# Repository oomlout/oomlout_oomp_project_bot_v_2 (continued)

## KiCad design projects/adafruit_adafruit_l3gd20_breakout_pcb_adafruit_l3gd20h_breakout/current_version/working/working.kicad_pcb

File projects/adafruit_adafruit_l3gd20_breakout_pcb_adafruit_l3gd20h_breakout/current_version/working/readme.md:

# adafruit_l3gd20_breakout_pcb
 
## summary 
* id: adafruit_adafruit_l3gd20_breakout_pcb_adafruit_l3gd20h_breakout
* user: adafruit
* name: adafruit_l3gd20_breakout_pcb
* board: adafruit_l3gd20h_breakout
* repo: https://github.com/adafruit/Adafruit-L3GD20-Breakout-PCB

* src_file_repo_sch: 
* src_file_repo_sch_link: https://github.com/adafruit/Adafruit-L3GD20-Breakout-PCB/tree/master/
* full details link: https://github.com/oomlout/oomlout_oomp_project_bot_v_2/tree/main/projects/adafruit_adafruit_l3gd20_breakout_pcb_adafruit_l3gd20h_breakout/current_version/working  

## schematic  
  
[schematic (pdf)](working_schematic.pdf) 

## pcb  

[board (pdf)](working.pdf)  

## working_bom
| Id | Designator | Footprint | Quantity | Designation | Supplier and ref |  | None | 
| --- | --- | --- | --- | --- | --- | --- | --- | 
| 1 | U$12,U$11,U$14,U$13 | MOUNTINGHOLE_2.0_PLATED | 4 | MOUNTINGHOLE2.0 |  |  | [''] | 
| 2 | U$15,U$16 | FIDUCIAL_1MM | 2 | FIDUCIAL |  |  | [''] | 
| 3 | R6,R3 | _0805MP | 2 | 10K |  |  | [''] | 
| 4 | R2,R5,R4,R7 | 0805-NO | 4 | 10K |  |  | [''] | 
| 5 | IC2 | L3GD20H_LGA16L | 1 | LGD20H |  |  | [''] | 
| 6 | C4,C1 | 0805-NO | 2 | 0.1uF |  |  | [''] | 
| 7 | D1 | SOD-323F | 1 | 1N4148 |  |  | [''] | 
| 8 | IC1 | SOT23-5L | 1 | MIC5225-3.3 |  |  | [''] | 
| 9 | U$3 | SYMBOL_GYROXYZ_10MM | 1 |  |  |  | [''] | 
| 10 | Q1,Q2 | SOT23 | 2 | BSS138 |  |  | [''] | 
| 11 | C5,C3 | 0805-NO | 2 | 10uF |  |  | [''] | 
| 12 | JP1 | 1X09_ROUND_76 | 1 |  |  |  | [''] | 
| 13 | U$10 | ADAFRUIT_TEXT_20MM | 1 |  |  |  | [''] | 

## bom_schematic
| Ref | Qnty | Value | Cmp name | Footprint | Description | Vendor | DNP | 
| --- | --- | --- | --- | --- | --- | --- | --- | 
| C1, C4 | 2 | 0.1uF | CAP_CERAMIC0805-NOOUTLINE | working:0805-NO |  |  |  | 
| C3, C5 | 2 | 10uF | CAP_CERAMIC0805-NOOUTLINE | working:0805-NO |  |  |  | 
| D1 | 1 | 1N4148 | DIODESOD-323F | working:SOD-323F |  |  |  | 
| IC1 | 1 | LP298XS | LP298XS | working:SOT23-5L |  |  |  | 
| IC2 | 1 | LGD20H | GYRO_L3GD20H | working:L3GD20H_LGA16L |  |  |  | 
| JP1 | 1 | HEADER-1X976MIL | HEADER-1X976MIL | working:1X09_ROUND_76 |  |  |  | 
| Q1, Q2 | 2 | BSS138 | MOSFET-NREFLOW | working:SOT23 |  |  |  | 
| R2, R4, R5, R7 | 4 | 10K | RESISTOR0805_NOOUTLINE | working:0805-NO |  |  |  | 
| R3, R6 | 2 | 10K | RESISTOR_0805MP | working:_0805MP |  |  |  | 
| U$11, U$12, U$13, U$14 | 4 | MOUNTINGHOLE2.0 | MOUNTINGHOLE2.0 | working:MOUNTINGHOLE_2.0_PLATED |  |  |  | 
| U$15, U$16 | 2 | FIDUCIAL | FIDUCIAL | working:FIDUCIAL_1MM |  |  |  | 

## mounting_holes
| x | y | package | value | ref | size | 
| --- | --- | --- | --- | --- | --- | 
| 25.4 | 12.83 | MOUNTINGHOLE_2.0_PLATED | MOUNTINGHOLE2.0 | U$11 | m3 | 
| 0.0 | 12.83 | MOUNTINGHOLE_2.0_PLATED | MOUNTINGHOLE2.0 | U$12 | m3 | 
| 0.0 | 0.0 | MOUNTINGHOLE_2.0_PLATED | MOUNTINGHOLE2.0 | U$13 | m3 | 
| 25.4 | 0.0 | MOUNTINGHOLE_2.0_PLATED | MOUNTINGHOLE2.0 | U$14 | m3 |

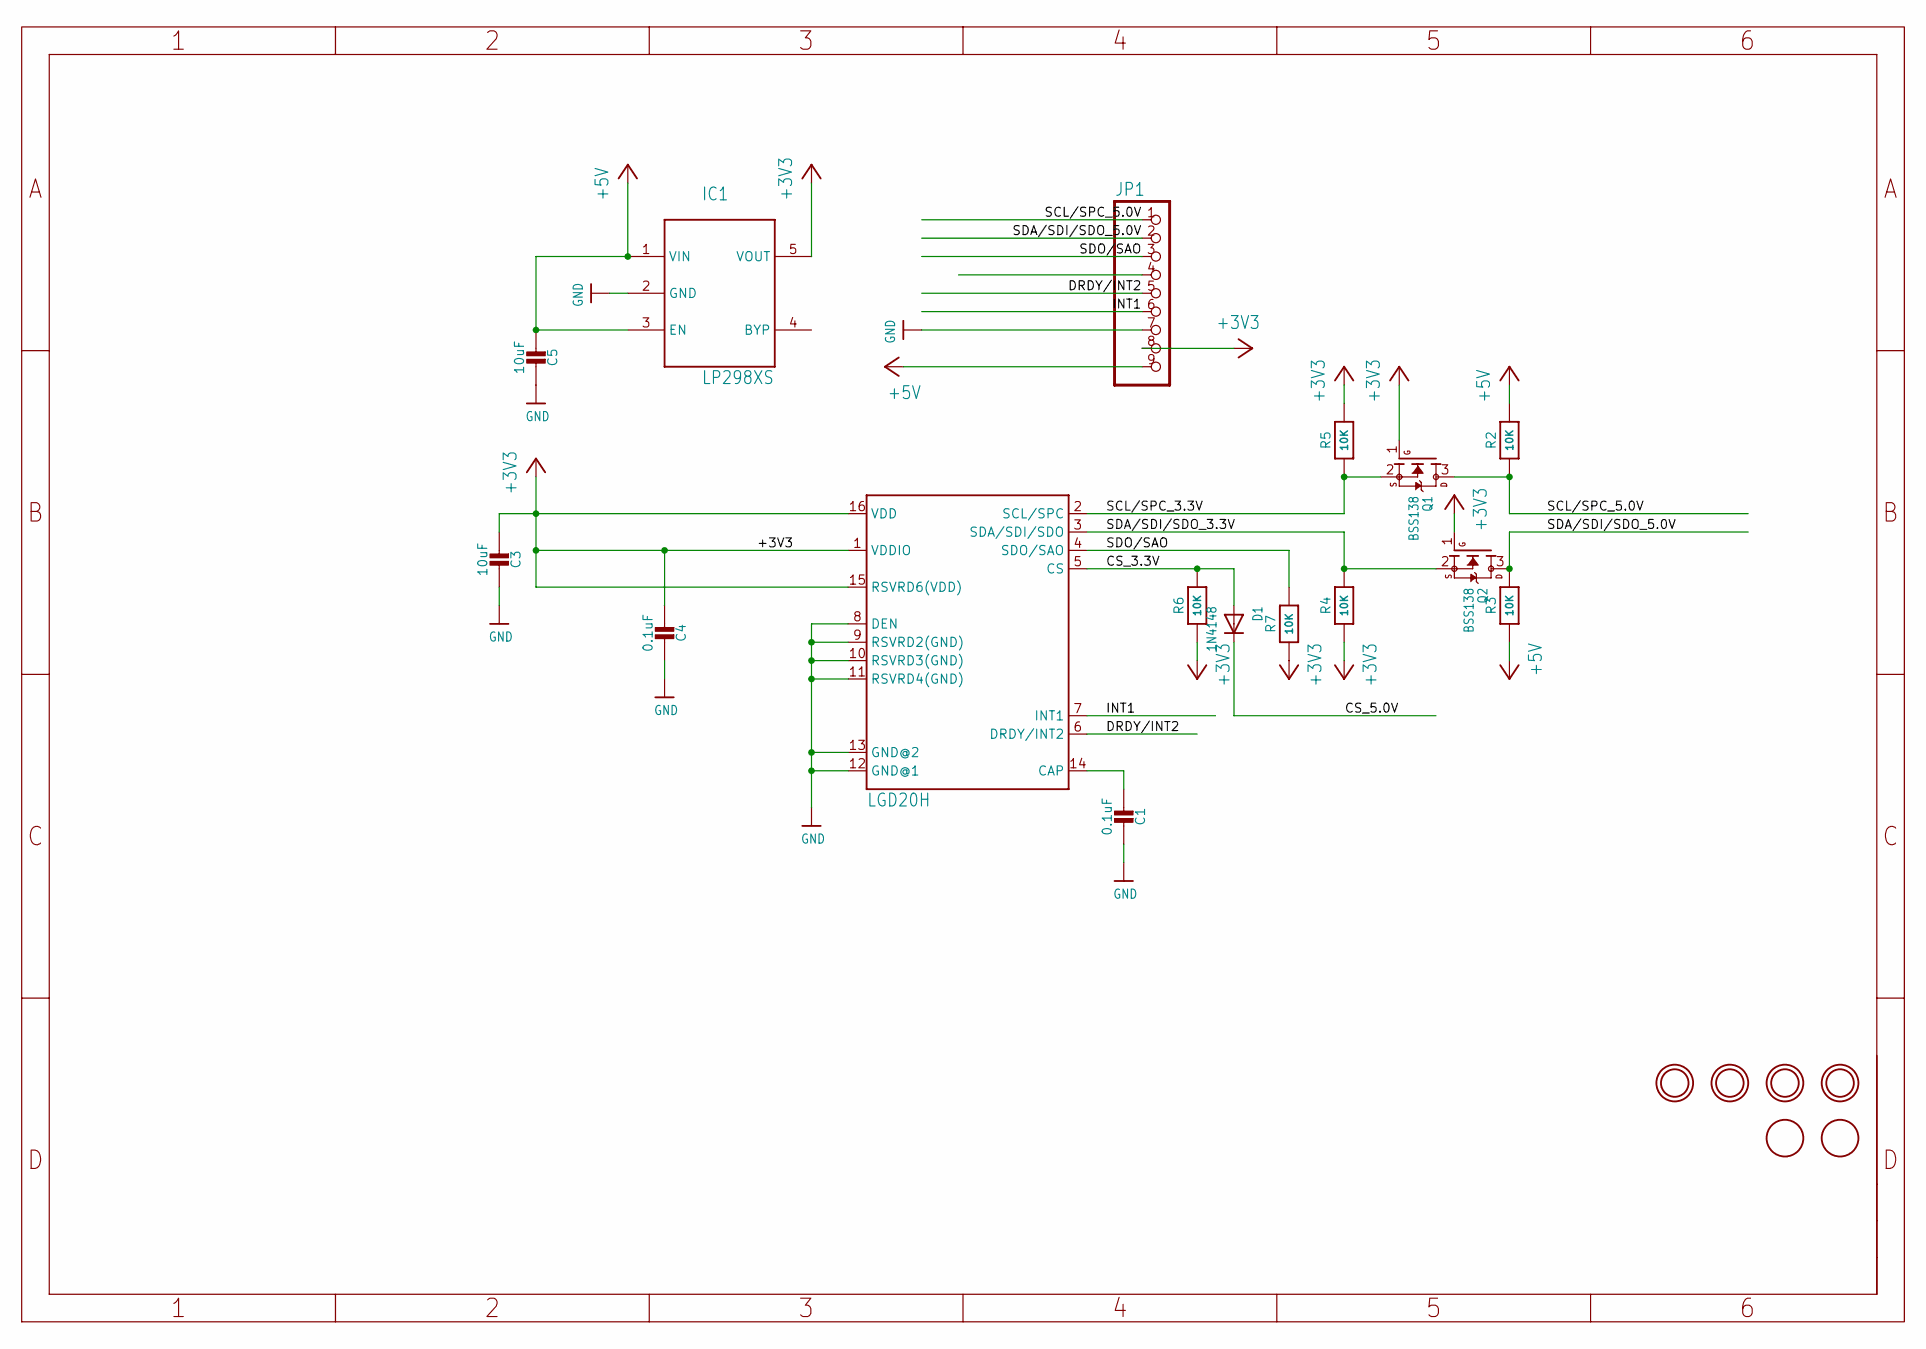
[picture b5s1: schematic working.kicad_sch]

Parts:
C1, C4: 0.1uF; 0805-NO
C3, C5: 10uF; 0805-NO
D1: 1N4148; SOD-323F
IC1: LP298XS; SOT23-5L
IC2: LGD20H; L3GD20H_LGA16L
JP1: HEADER-1X976MIL; 1X09_ROUND_76
Q1, Q2: BSS138; SOT23
R2, R4, R5, R7: 10K; 0805-NO
R3, R6: 10K; _0805MP
U$11, U$12, U$13, U$14: MOUNTINGHOLE2.0; MOUNTINGHOLE_2.0_PLATED
U$15, U$16: FIDUCIAL; FIDUCIAL_1MM

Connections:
+3V3: C3.2, C4.2, IC1.5 (VOUT), IC2.1 (VDDIO), IC2.15 (RSVRD6(VDD)), IC2.16 (VDD), JP1.8, Q1.1 (G), Q2.1 (G), R4.1, R5.2, R6.1, R7.1
+5V: C5.2, IC1.1 (VIN), IC1.3 (EN), JP1.9, R2.2, R3.1
CS_3.3V: D1.A, IC2.5 (CS), R6.2
CS_5.0V: D1.C, JP1.4
DRDY/INT2: IC2.6 (DRDY/INT2), JP1.5
GND: C1.1, C3.1, C4.1, C5.1, IC1.2 (GND), IC2.8 (DEN), IC2.9 (RSVRD2(GND)), IC2.10 (RSVRD3(GND)), IC2.11 (RSVRD4(GND)), IC2.12 (GND@1), IC2.13 (GND@2), JP1.7
INT1: IC2.7 (INT1), JP1.6
unnamed: C1.2, IC2.14 (CAP)
SCL/SPC_3.3V: IC2.2 (SCL/SPC), Q1.2 (S), R5.1
SCL/SPC_5.0V: JP1.1, Q1.3 (D), R2.1
SDA/SDI/SDO_3.3V: IC2.3 (SDA/SDI/SDO), Q2.2 (S), R4.2
SDA/SDI/SDO_5.0V: JP1.2, Q2.3 (D), R3.2
SDO/SAO: IC2.4 (SDO/SAO), JP1.3, R7.2

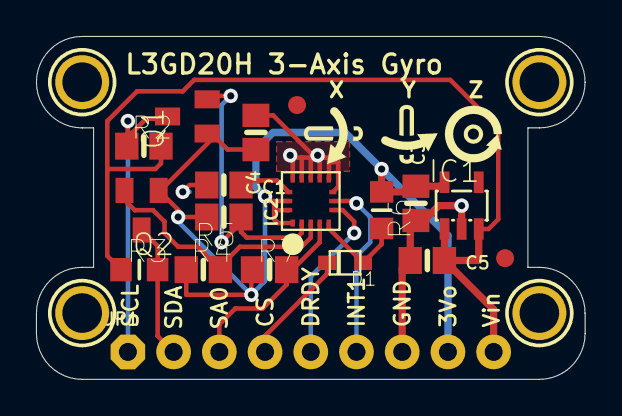
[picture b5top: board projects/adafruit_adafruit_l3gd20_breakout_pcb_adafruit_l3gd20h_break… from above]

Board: 2 copper layers, 30.5 x 19.0 mm, 24 parts (1 on the bottom side), 13 nets.

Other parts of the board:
U$3: SYMBOL_GYROXYZ_10MM
U$10: ADAFRUIT_TEXT_20MM

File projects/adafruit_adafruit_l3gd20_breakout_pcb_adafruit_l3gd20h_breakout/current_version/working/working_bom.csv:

"Id";"Designator";"Footprint";"Quantity";"Designation";"Supplier and ref";
1;"U$12,U$11,U$14,U$13";"MOUNTINGHOLE_2.0_PLATED";4;"MOUNTINGHOLE2.0";;;
2;"U$15,U$16";"FIDUCIAL_1MM";2;"FIDUCIAL";;;
3;"R6,R3";"_0805MP";2;"10K";;;
4;"R2,R5,R4,R7";"0805-NO";4;"10K";;;
5;"IC2";"L3GD20H_LGA16L";1;"LGD20H";;;
6;"C4,C1";"0805-NO";2;"0.1uF";;;
7;"D1";"SOD-323F";1;"1N4148";;;
8;"IC1";"SOT23-5L";1;"MIC5225-3.3";;;
9;"U$3";"SYMBOL_GYROXYZ_10MM";1;"";;;
10;"Q1,Q2";"SOT23";2;"BSS138";;;
11;"C5,C3";"0805-NO";2;"10uF";;;
12;"JP1";"1X09_ROUND_76";1;"";;;
13;"U$10";"ADAFRUIT_TEXT_20MM";1;"";;;

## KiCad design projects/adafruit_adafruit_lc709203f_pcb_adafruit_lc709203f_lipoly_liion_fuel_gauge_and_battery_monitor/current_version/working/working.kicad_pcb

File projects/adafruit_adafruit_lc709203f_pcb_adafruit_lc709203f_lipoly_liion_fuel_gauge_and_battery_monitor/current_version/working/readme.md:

# adafruit_lc709203f_pcb
 
## summary 
* id: adafruit_adafruit_lc709203f_pcb_adafruit_lc709203f_lipoly_liion_fuel_gauge_and_battery_monitor
* user: adafruit
* name: adafruit_lc709203f_pcb
* board: adafruit_lc709203f_lipoly_liion_fuel_gauge_and_battery_monitor
* repo: https://github.com/adafruit/Adafruit-LC709203F-PCB

* src_file_repo_sch: 
* src_file_repo_sch_link: https://github.com/adafruit/Adafruit-LC709203F-PCB/tree/master/
* full details link: https://github.com/oomlout/oomlout_oomp_project_bot_v_2/tree/main/projects/adafruit_adafruit_lc709203f_pcb_adafruit_lc709203f_lipoly_liion_fuel_gauge_and_battery_monitor/current_version/working  

## schematic  
  
[schematic (pdf)](working_schematic.pdf) 

## pcb  

[board (pdf)](working.pdf)  

## working_bom
| Id | Designator | Footprint | Quantity | Designation | Supplier and ref |  | None | 
| --- | --- | --- | --- | --- | --- | --- | --- | 
| 1 | U$21,U$19 | MOUNTINGHOLE_2.5_PLATED | 2 | MOUNTINGHOLE2.5 |  |  | [''] | 
| 2 | CONN3,CONN4 | JST_SH4 | 2 | STEMMA_I2C_QT |  |  | [''] | 
| 3 | @HOLE1,@HOLE0 |  | 2 |  |  |  | [''] | 
| 4 | X1,X2 | JSTPH2_BATT | 2 | JST 2 PH |  |  | [''] | 
| 5 | JP1 | 1X06_ROUND_70 | 1 |  |  |  | [''] | 
| 6 | D1 | CHIPLED_0603_NOOUTLINE | 1 | GREEN |  |  | [''] | 
| 7 | FID4,FID3 | FIDUCIAL_1MM | 2 | FIDUCIAL_1MM |  |  | [''] | 
| 8 | IC1 | WDFN8_3X4_0.65 | 1 | LC709203F |  |  | [''] | 
| 9 | R4 | 0603-NO | 1 | 100 |  |  | [''] | 
| 10 | C1 | 0603-NO | 1 | 1uF |  |  | [''] | 
| 11 | R3 | RESPACK_4X0603 | 1 | 10K |  |  | [''] | 
| 12 | U$22 | ADAFRUIT_3.5MM | 1 |  |  |  | [''] | 
| 13 | R1 | 0603-NO | 1 | 10K |  |  | [''] | 
| 14 | SJ1 | SOLDERJUMPER_CLOSEDWIRE | 1 |  |  |  | [''] | 
| 15 | U$25 | PCBFEAT-REV-040 | 1 |  |  |  | [''] | 
| 16 | U$30,U$31 | STEMMAQT | 2 |  |  |  | [''] | 

## bom_schematic
| Ref | Qnty | Value | Cmp name | Footprint | Description | Vendor | DNP | 
| --- | --- | --- | --- | --- | --- | --- | --- | 
| C1 | 1 | 1uF | CAP_CERAMIC0603_NO | working:0603-NO |  |  |  | 
| CONN3, CONN4 | 2 | STEMMA_I2C_QT | STEMMA_I2C_QT | working:JST_SH4 |  |  |  | 
| D1 | 1 | GREEN | LED0603_NOOUTLINE | working:CHIPLED_0603_NOOUTLINE |  |  |  | 
| FID3, FID4 | 2 | FIDUCIAL_1MM | FIDUCIAL_1MM | working:FIDUCIAL_1MM |  |  |  | 
| IC1 | 1 | LC709203F | LC709203F | working:WDFN8_3X4_0.65 |  |  |  | 
| JP1 | 1 | HEADER-1X670MIL | HEADER-1X670MIL | working:1X06_ROUND_70 |  |  |  | 
| R1 | 1 | 10K | RESISTOR_0603_NOOUT | working:0603-NO |  |  |  | 
| R3 | 1 | 10K | RESISTOR_4PACK | working:RESPACK_4X0603 |  |  |  | 
| R4 | 1 | 100 | RESISTOR_0603_NOOUT | working:0603-NO |  |  |  | 
| SJ1 | 1 | SOLDERJUMPERCLOSED | SOLDERJUMPERCLOSED | working:SOLDERJUMPER_CLOSEDWIRE |  |  |  | 
| U$19, U$21 | 2 | MOUNTINGHOLE2.5 | MOUNTINGHOLE2.5 | working:MOUNTINGHOLE_2.5_PLATED |  |  |  | 
| X1, X2 | 2 | JST 2 PH | CON_JST_PH_2PIN_BATT | working:JSTPH2_BATT |  |  |  | 

## mounting_holes
| x | y | package | value | ref | size | 
| --- | --- | --- | --- | --- | --- | 
| 0.0 | 0.0 | MOUNTINGHOLE_2.5_PLATED | MOUNTINGHOLE2.5 | U$19 | m3 | 
| 20.32 | 0.0 | MOUNTINGHOLE_2.5_PLATED | MOUNTINGHOLE2.5 | U$21 | m3 |

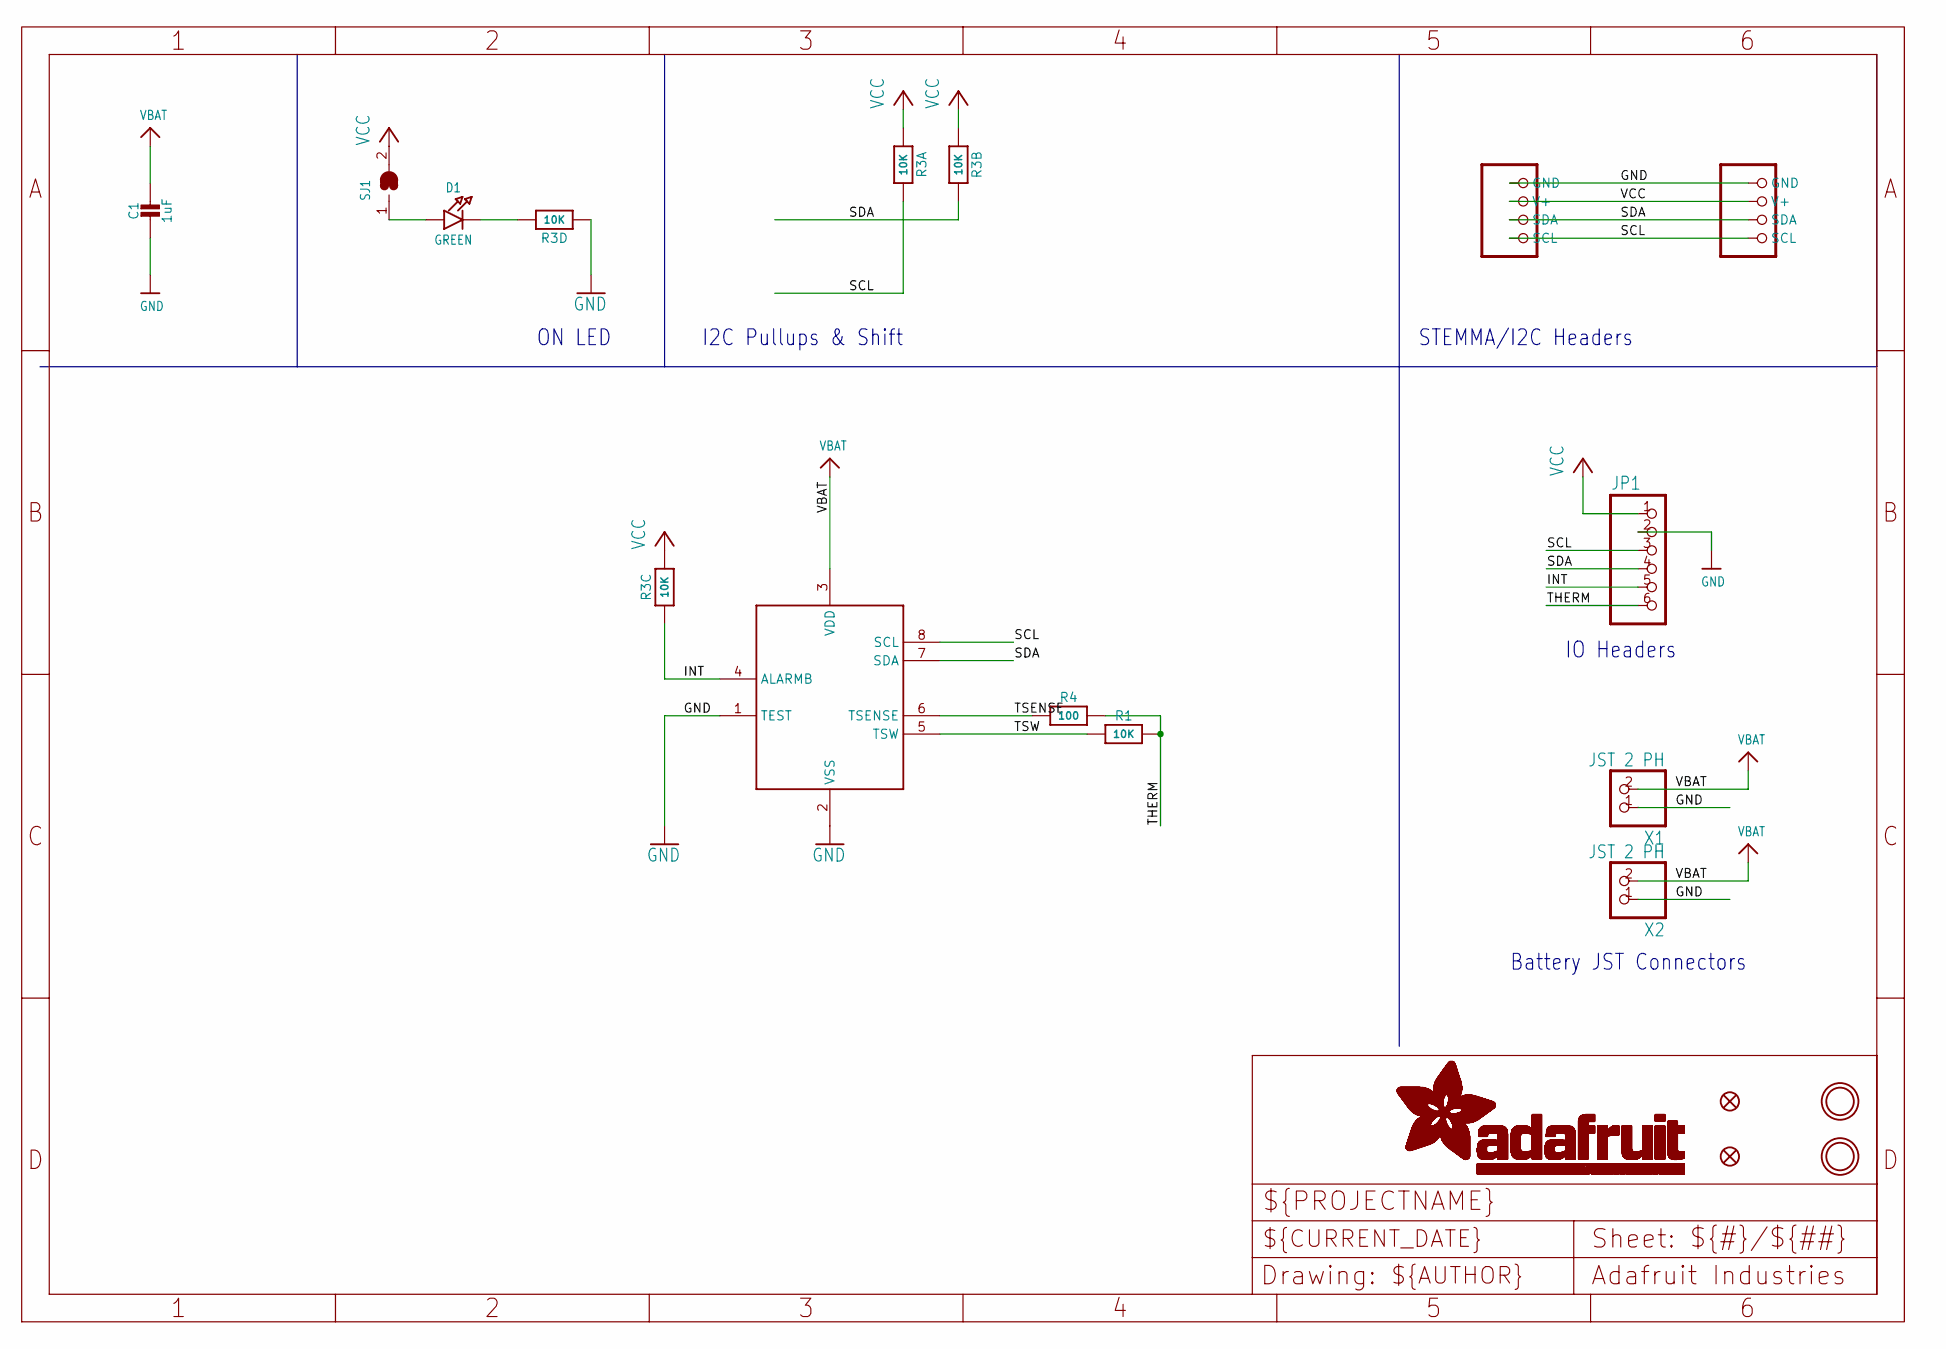
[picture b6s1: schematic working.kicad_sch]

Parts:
C1: 1uF; 0603-NO
CONN3, CONN4: STEMMA_I2C_QT; JST_SH4
D1: GREEN; CHIPLED_0603_NOOUTLINE
FID3, FID4: FIDUCIAL_1MM
IC1: LC709203F; WDFN8_3X4_0.65
JP1: HEADER-1X670MIL; 1X06_ROUND_70
R1: 10K; 0603-NO
R3: 10K; RESPACK_4X0603
R4: 100; 0603-NO
SJ1: SOLDERJUMPERCLOSED; SOLDERJUMPER_CLOSEDWIRE
U$19, U$21: MOUNTINGHOLE2.5; MOUNTINGHOLE_2.5_PLATED
X1, X2: JST 2 PH; JSTPH2_BATT

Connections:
GND: C1.2, CONN3.1 (GND), CONN4.1 (GND), IC1.1 (TEST), IC1.2 (VSS), JP1.2, R3.4 (1), X1.1, X2.1
INT: IC1.4 (ALARMB), JP1.5, R3.3 (1)
unnamed: D1.C, R3.5 (2)
unnamed: D1.A, SJ1.1
SCL: CONN3.4 (SCL), CONN4.4 (SCL), IC1.8 (SCL), JP1.3, R3.8 (2)
SDA: CONN3.3 (SDA), CONN4.3 (SDA), IC1.7 (SDA), JP1.4, R3.7 (2)
THERM: JP1.6, R1.2, R4.2
TSENSE: IC1.6 (TSENSE), R4.1
TSW: IC1.5 (TSW), R1.1
VBAT: C1.1, IC1.3 (VDD), X1.2, X2.2
VCC: CONN3.2 (V+), CONN4.2 (V+), JP1.1, R3.1, R3.2 (1), R3.6 (2), SJ1.2

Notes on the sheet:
STEMMA/I2C Headers
ON LED
I2C Pullups & Shift
Battery JST Connectors
IO Headers

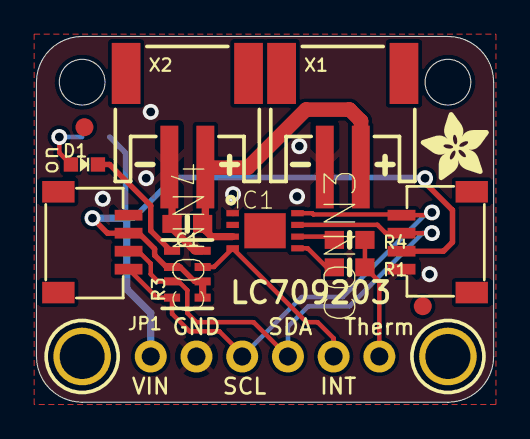
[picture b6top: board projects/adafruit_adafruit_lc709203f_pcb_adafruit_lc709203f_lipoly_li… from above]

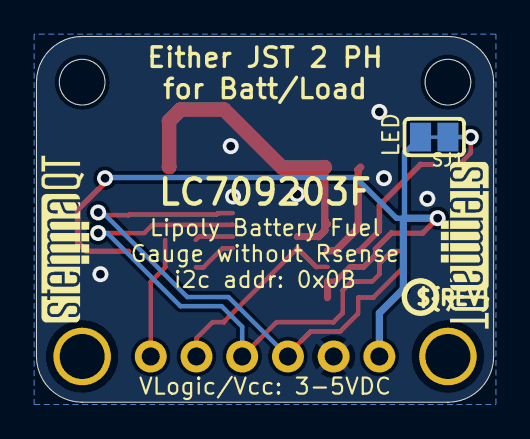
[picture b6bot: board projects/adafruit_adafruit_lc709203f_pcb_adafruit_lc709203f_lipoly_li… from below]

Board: 2 copper layers, 25.4 x 20.3 mm, 22 parts (4 on the bottom side), 11 nets.

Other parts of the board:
@HOLE0, @HOLE1: (no value)
U$22: ADAFRUIT_3.5MM
U$25: PCBFEAT-REV-040
U$30, U$31: STEMMAQT

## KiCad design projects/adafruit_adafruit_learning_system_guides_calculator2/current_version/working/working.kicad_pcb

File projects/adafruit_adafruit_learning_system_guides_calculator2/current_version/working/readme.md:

# adafruit_learning_system_guides
 
## summary 
* id: adafruit_adafruit_learning_system_guides_calculator2
* user: adafruit
* name: adafruit_learning_system_guides
* board: calculator2
* repo: https://github.com/adafruit/Adafruit_Learning_System_Guides
* src_file_repo_kicad_pcb: CircuitPython_KeyPad_Calculator/design-files/pcb/calculator2/calculator2-rounded.kicad_pcb
* src_file_repo_kicad_pcb_link: https://github.com/adafruit/Adafruit_Learning_System_Guides/tree/main/CircuitPython_KeyPad_Calculator/design-files/pcb/calculator2/calculator2-rounded.kicad_pcb

* src_file_repo_sch: 
* src_file_repo_sch_link: https://github.com/adafruit/Adafruit_Learning_System_Guides/tree/main/
* full details link: https://github.com/oomlout/oomlout_oomp_project_bot_v_2/tree/main/projects/adafruit_adafruit_learning_system_guides_calculator2/current_version/working  

## pcb  

[board (pdf)](working.pdf)  

## working_bom
| Id | Designator | Footprint | Quantity | Designation | Supplier and ref |  | None | 
| --- | --- | --- | --- | --- | --- | --- | --- | 
| 1 | U1 | ADAFRUIT_FEATHER | 1 | ADAFRUIT_FEATHER |  |  | [''] | 
| 2 | D1,D2,D3,D4,D5,D6,D7,D8,D9,D10,D11,D12,D13,D14,D15,D16,D17,D18,D19,D20 | D_DO-41_SOD81_P10.16mm_Horizontal | 20 | D |  |  | [''] | 
| 3 | SW1,SW2,SW3,SW4,SW5,SW6,SW7,SW8,SW9,SW10,SW11,SW12,SW13,SW14,SW15,SW16,SW17,SW18,SW19,SW20 | SW_Cherry_MX_1.00u_PCB | 20 | SW_Push |  |  | [''] |

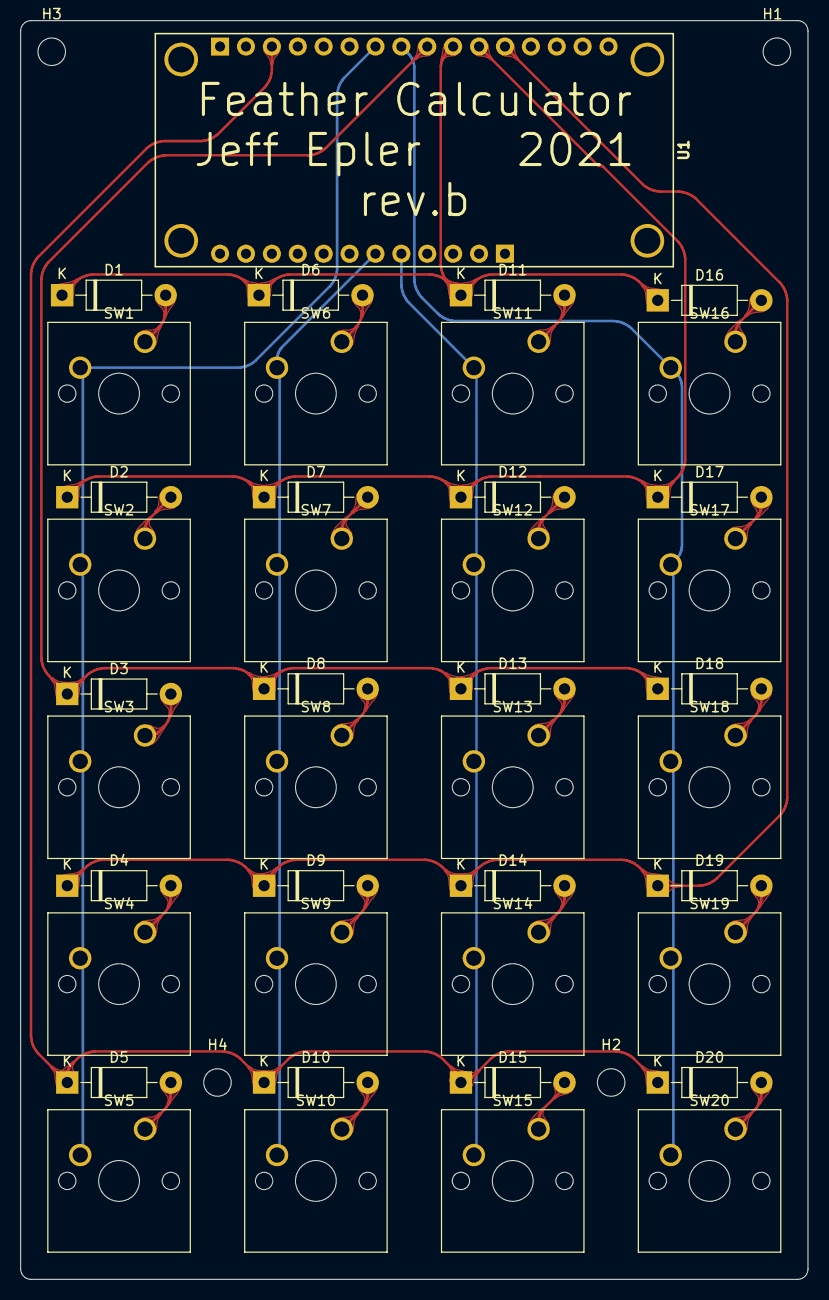
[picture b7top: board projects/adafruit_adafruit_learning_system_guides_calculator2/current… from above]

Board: 2 copper layers, 77.2 x 123.4 mm, 45 parts (0 on the bottom side), 29 nets.

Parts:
D1, D2, D3, D4, D5, D6, D7, D8, D9, D10, D11, D12, D13, D14, D15, D16, D17, D18, D19, D20: D; D_DO-41_SOD81_P10.16mm_Horizontal
H1, H2, H3, H4: MountingHole; MountingHole_2.7mm_M2.5
SW1, SW2, SW3, SW4, SW5, SW6, SW7, SW8, SW9, SW10, SW11, SW12, SW13, SW14, SW15, SW16, SW17, SW18, SW19, SW20: SW_Push; SW_Cherry_MX_1.00u_PCB
U1: ADAFRUIT_FEATHER

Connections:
/C1: SW16.2, SW17.2, SW18.2, SW19.2, SW20.2, U1.8
/C2: SW11.2, SW12.2, SW13.2, SW14.2, SW15.2, U1.21
/C3: SW6.2, SW7.2, SW8.2, SW9.2, SW10.2, U1.22
/C4: SW1.2, SW2.2, SW3.2, SW4.2, SW5.2, U1.7
/R1: D1.1, D6.1, D11.1, D16.1, U1.10
/R2: D2.1, D7.1, D12.1, D17.1, U1.11
/R3: D3.1, D8.1, D13.1, D18.1, U1.9
/R4: D4.1, D9.1, D14.1, D19.1, U1.12
/R5: D5.1, D10.1, D15.1, D20.1, U1.3
unnamed: D1.2, SW1.1
unnamed: D2.2, SW2.1
unnamed: D3.2, SW3.1
unnamed: D4.2, SW4.1
unnamed: D5.2, SW5.1
unnamed: D6.2, SW6.1
unnamed: D7.2, SW7.1
unnamed: D8.2, SW8.1
unnamed: D9.2, SW9.1
unnamed: D10.2, SW10.1
unnamed: D11.2, SW11.1
unnamed: D12.2, SW12.1
unnamed: D13.2, SW13.1
unnamed: D14.2, SW14.1
unnamed: D15.2, SW15.1
unnamed: D16.2, SW16.1
unnamed: D17.2, SW17.1
unnamed: D18.2, SW18.1
unnamed: D19.2, SW19.1
unnamed: D20.2, SW20.1
